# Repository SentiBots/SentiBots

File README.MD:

The SentiBots project is a project aiming to achieve the perfect distributed robotic system 
platform. By providing open source files we allow the end user to modify the files as necessary 
to his/her needs. This project invovles a custom designed frame and build which creates a 
modular, optimised frame for a distributed robotic system.

This is the source files for the SentiBots project. It includes the source code, cad files, build
notes and documentation you might need. 

# Cloning

```
git clone ssh://git@makerforce.io:222/SentiBots/SentiBots.git
cd SentiBots
git submodule init
git submodule update
```

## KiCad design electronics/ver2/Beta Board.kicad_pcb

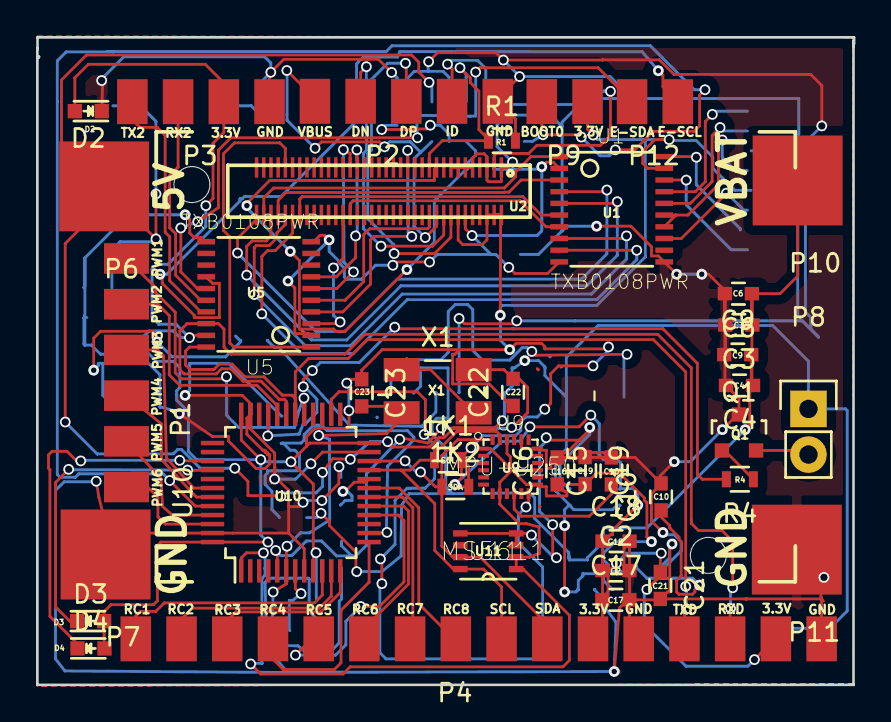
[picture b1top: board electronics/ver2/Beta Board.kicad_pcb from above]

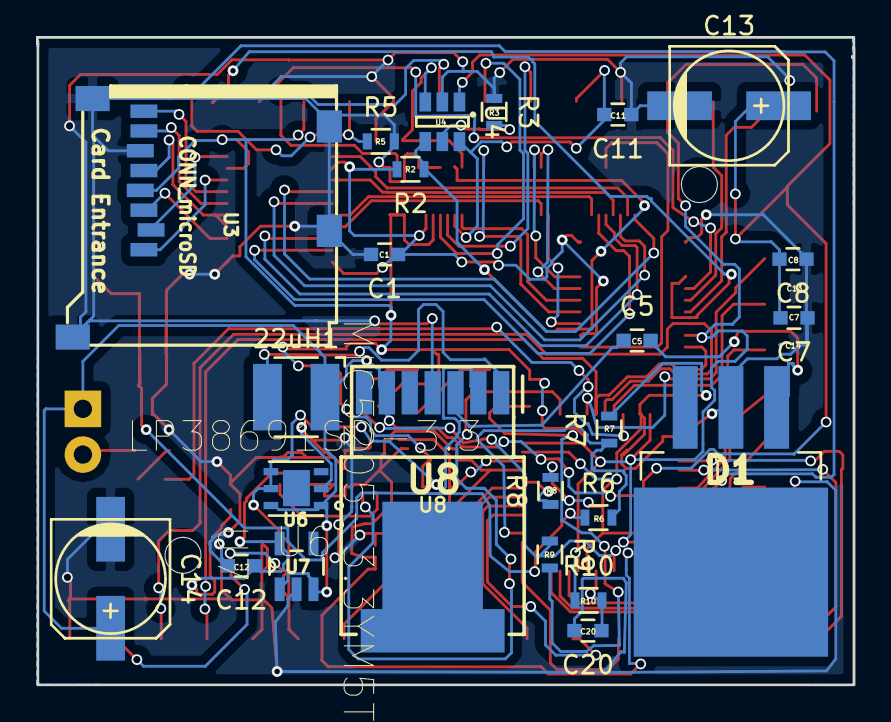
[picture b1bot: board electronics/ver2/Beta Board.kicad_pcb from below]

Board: 2 copper layers, 45.4 x 36.0 mm, 64 parts (24 on the bottom side), 71 nets.

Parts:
1K1, 1K2: R; R_0603
22uH1: INDUCTOR; NR4018
C1, C2, C8, C12, C15, C16, C17, C20, C21: 0.1uF; C_0603
C3, C4, C6: 15uF; C_0603
C5: 0.01uF; C_0603
C7: 1uF; C_0603
C9: 0.47uF; C_0603
C10: 10uF; C_0603
C11: 2.2uF; C_0603
C13, C14: 180uF; c_elec_6.3x5.8
C18, C19: 10nF; C_0603
C22, C23: 27pF; C_0603
D1: 6TQ045S; TO-263-3Lead
D2: RED; LED_0603
D3: GREEN; LED_0603
D4: YELLOW; LED_0603
P1: PWM; PAD1X6
P2: USB OTG; PAD1X5
P3: UART EDISON; PAD1X4
P4: MCU GPIO; PAD1X16
P6: 5V; PADBIG
P7, P11: GND; PADBIG
P8: BUZZER; Pin_Header_Straight_1x02
P9: BOOT; PAD1X2
P10: V_BATT; PADBIG
P12: I2C_EDISON; PAD1X2
Q1: MMBT3906; SOT-23
R1: 100K; R_0603
R2, R10: 10K; R_0603
R3: 536; R_0603
R4: 100R; R_0603
R5, R7, R8: 1K; R_0603
R6: 10k; R_0603
R9: 1M; R_0603
U1, U5: TXB0108PWR; TSSOP20
U2: EdisonConnector; EDISON_DAUGHTER
U3: CONN_microSD; Memory_Card_microSD_3M_290805
U4: MIC2039; SOT-23-6
U6: LP38691SD-3.3; DFN300X300X80-7N
U7: MIC5205-3.3YM5TR; SOT95P280X130-5N
U8: LM2678T-5.0; TO-263-7-TEXAS
U9: MPU-9250; QFN-24%2f3MM
U10: STM32F103CB; LQFP-48_7x7mm_Pitch0.5mm
U11: MS5611; QFN-8
X1: 8.000MHz/20p; Crystal_SMD_5032_4Pads

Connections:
1.8V: C1.1, R2.2, U1.2, U1.10, U2.12, U5.2, U5.10
3.3V: 1K1.2, 1K2.2, C2.1, C17.1, C18.1, C21.1, C22.1, C23.1, D2.2, D3.2, D4.2, P3.3, P4.11, P4.15, P9.2, R10.1, U1.19, U2.2, U2.4, U2.6, U2.14, U3.4, U5.19, U6.4, U6.5, U10.9, U10.24, U10.36, U10.48
3.3V_SEN: C10.1, C12.1, C16.1, C19.2, U7.5, U9.1, U9.8, U9.13, U9.22, U10.1, U11.1, U11.2
5V: 22uH1.1, C7.2, C8.2, C13.1, C14.1, P6.1, P8.1, U4.1, U6.1, U6.6, U7.1, U7.3, U8.6
BEEP: R4.2, U10.33
BOOT0: P9.1, R5.1, U10.44
BOOT1: R8.1, U10.20
EDI_RX: U2.61, U5.1
EDI_RX2: U2.22, U5.5
EDI_SCL1: U2.41, U5.7
EDI_SDA1: U2.43, U5.6
EDI_TX: U2.46, U5.3
EDI_TX2: U2.27, U5.4
FAULT: R2.1, U2.19, U4.4
GND: C1.2, C2.2, C3.2, C4.2, C6.2, C7.1, C8.1, C9.1, C10.2, C11.1, C12.2, C13.2, C14.2, C15.2, C16.2, C17.2, C18.2, C19.1, C20.2, C21.2, D1.2, D2.1, P2.5, P3.4, P4.12, P4.16, P7.1, P11.1, Q1.3, R1.2, R3.1, R5.2, R7.2, R8.2, U1.11, U2.1, U2.5, U2.9, U2.11, U2.13, U2.15, U3.6, U3.9, U4.2, U5.11, U6.2, U7.2, U8.4, U9.18, U9.20, U10.8, U10.23, U10.35, U10.47, U11.3, U11.4, U11.5
LED0: D3.1, U10.40
LED1: D4.1, U10.39
MPU_INT: U9.12, U10.26
NRST: C20.1, R10.2, U10.7
unnamed: 22uH1.2, U8.1
unnamed: C5.1, U8.3
unnamed: C5.2, D1.1
unnamed: C15.1, U9.10
unnamed: P8.2, Q1.2
unnamed: P12.1, U5.15
unnamed: P12.2, U5.14
unnamed: Q1.1, R4.1
unnamed: R3.2, U4.5
unnamed: U1.13, U3.3
unnamed: U1.14, U1.15, U3.5
unnamed: U1.16, U3.7
unnamed: U1.17, U3.8
unnamed: U1.18, U3.1
unnamed: U1.20, U3.2
OSC_IN: C22.2, R9.1, U10.5, X1.2
OSC_OUT: C23.2, R9.2, U10.6, X1.1
POWER_ADC: R6.2, R7.1, U10.14
PSW: R1.1, U2.21, U4.3
PWM1: P1.6, U10.29
PWM2: P1.5, U10.32
PWM3: P1.4, U10.42
PWM4: P1.3, U10.43
PWM5: P1.2, U10.45
PWN6: P1.1, U10.46
RC_CH1: P4.1, U10.10
RC_CH2: P4.2, U10.11
RC_CH3: P4.3, U10.12
RC_CH4: P4.4, U10.13
RC_CH5: P4.5, U10.16
RC_CH6: P4.6, U10.17
RC_CH7: P4.7, U10.18
RC_CH8: P4.8, U10.19
RX2: P3.2, U5.16
RXD: P4.14, U5.18, U10.31
SCL: 1K1.1, P4.9, U9.23, U10.21, U11.8
SDA: 1K2.1, P4.10, U9.24, U10.22, U11.7
SD_0_CD#: U1.9, U2.60
SD_0_CLK: U1.6, U2.58
SD_0_CMD: U1.8, U2.62
SD_0_DA3: U1.1, U2.68
SD_0_DAT0: U1.5, U2.66
SD_0_DAT1: U1.4, U2.70
SD_0_DAT2: U1.3, U2.64
SD_CLK_FB: U1.7, U2.44
TX2: P3.1, U5.17
TXD: P4.13, U5.20, U10.30
USB_DN: P2.2, U2.18
USB_DP: P2.3, U2.16
USB_ID: P2.4, U2.3
VBAT: C3.1, C4.1, C6.1, C9.2, P10.1, R6.1, U8.2
V_BUS: C11.2, P2.1, U2.20, U4.6

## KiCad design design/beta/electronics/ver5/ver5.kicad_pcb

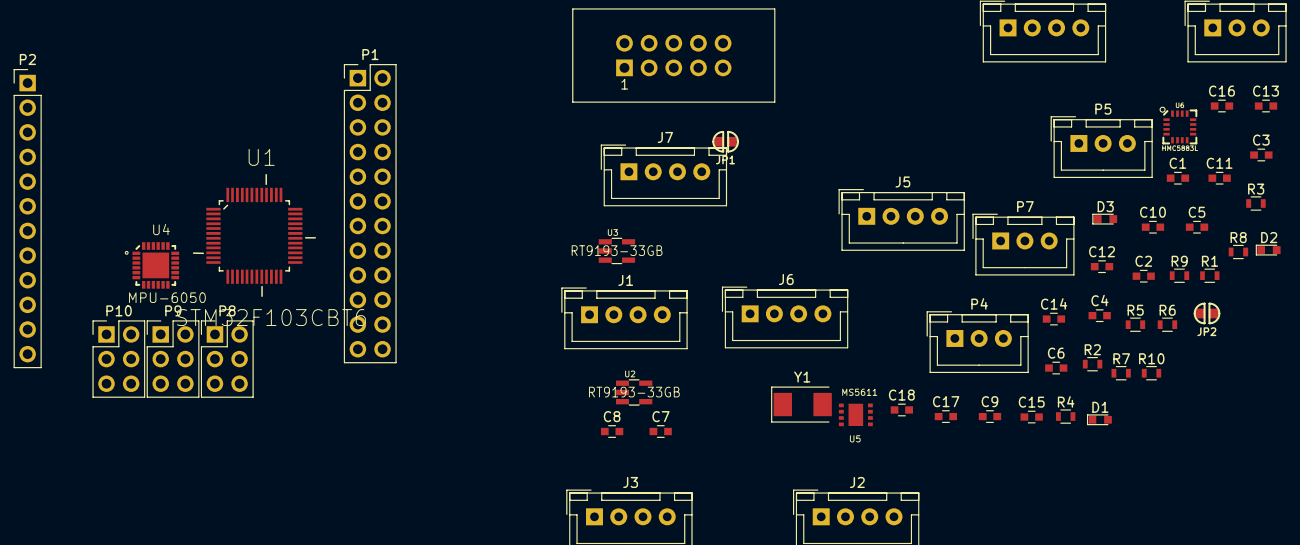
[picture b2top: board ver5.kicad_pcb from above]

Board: 2 copper layers, 57 parts (0 on the bottom side), 48 nets, no tracks yet.

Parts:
C1, C2, C3, C4: 10uF; C_0603
C5, C6, C9, C11, C12, C13, C16, C17, C18: 0.1uF; C_0603
C7: 4.7uF; C_0603
C8: 0.22uF; C_0603
C10: 2.2uF; C_0603
C14, C15: 18pF; C_0603
D1: BLUE; LED_0603
D2: RED; LED_0603
D3: GREEN; LED_0603
J1: NANOPI_UART2; JST_XH_B04B-XH-A_04x2.50mm_Straight
J2: NANOPI_USB1; JST_XH_B04B-XH-A_04x2.50mm_Straight
J3: NANOPI_USB2; JST_XH_B04B-XH-A_04x2.50mm_Straight
J4: STM32_I2C1; JST_XH_B04B-XH-A_04x2.50mm_Straight
J5: NANOPI_I2C1; JST_XH_B04B-XH-A_04x2.50mm_Straight
J6: STM32_UART1; JST_XH_B04B-XH-A_04x2.50mm_Straight
J7: STM32_UART2; JST_XH_B04B-XH-A_04x2.50mm_Straight
JP1, JP2: JUMPER; SOLDER-JUMPER_1-WAY
P1: NANOPI; Pin_Header_Straight_2x12_Pitch2.54mm
P2: NANOPI; Pin_Header_Straight_1x12_Pitch2.54mm
P3: JTAG; IDC_Header_Straight_10pins
P4: IR1; JST_XH_B03B-XH-A_03x2.50mm_Straight
P5: IR2; JST_XH_B03B-XH-A_03x2.50mm_Straight
P6: IR3; JST_XH_B03B-XH-A_03x2.50mm_Straight
P7: IR4; JST_XH_B03B-XH-A_03x2.50mm_Straight
P8: MOTORS1; Pin_Header_Straight_2x03_Pitch2.54mm
P9: MOTORS2; Pin_Header_Straight_2x03_Pitch2.54mm
P10: MOTORS3; Pin_Header_Straight_2x03_Pitch2.54mm
R1, R2, R3: 1K; R_0603
R4, R8, R10: R; R_0603
R5, R6, R9: 10K; R_0603
R7: 1k; R_0603
U1: STM32F103CBT6; QFP50P900X900X160-48N
U2, U3: RT9193-33GB; SOT-23-5
U4: MPU-6050; QFN50P400X400X95-25N
U5: MS5611; QFN-8
U6: HMC5883L; LPCC-16
Y1: 8MHz; Crystal_SMD_Abracon_ABM3-2pin_5.0x3.2mm

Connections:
+3V3: P1.1, P1.17
+5V: C1.1, C2.1, J2.3, J3.3, P1.2, P1.4, P8.3, P8.4, P9.3, P9.4, P10.3, P10.4
/BOOT0: JP2.1, R9.2, U1.44
/BOOT1: JP1.1, R5.2, U1.20
/CLK: P1.23, P6.1
/CS: P1.24, P7.1
/LED0: R8.2, U1.40
/LED1: R10.2, U1.39
/MISO: P1.21, P5.1
/MOSI: P1.19, P4.1
/MPU_INT: U1.26, U4.12
/NRST: P3.10, U1.7
/OSC_IN: C14.1, U1.5, Y1.1
/OSC_OUT: C15.1, U1.6, Y1.2
/PIUART1_TX: J6.2, P1.8, U1.31
/PIUART_RX: J6.1, P1.10, U1.30
/PIUART_RX2: J1.2, P1.22
/PIUART_TX2: J1.1, P1.11
/PI_SCL: J5.1, P1.5
/PI_SDA: J5.2, P1.3
/POWER_ADC: R6.2, R7.1, U1.14
/PWM1: P8.1, U1.29
/PWM2: P8.2, U1.32
/PWM3: P9.1, U1.42
/PWM4: P9.2, U1.43
/PWM5: P10.1, U1.45
/PWM6: P10.2, U1.46
/RX2: J7.2, U1.13
/SCL: J4.1, R2.2, R3.2, U1.21, U4.23, U5.8, U6.1
/SDA: J4.2, R1.2, U1.22, U4.24, U5.7, U6.16
/SWDCLK: P3.4, U1.37
/SWDIO: P3.2, U1.34
/TX2: J7.1, U1.12
/USB1_DN: J2.2, P2.10
/USB1_DP: J2.1, P2.11
/USB2_DN: J3.2, P2.8
/USB2_DP: J3.1, P2.9
/VCC_SENSE: C3.1, C5.1, C11.1, U4.13, U5.1, U5.2, U6.2
GND: C1.2, C2.2, C3.2, C4.2, C5.2, C6.2, C7.2, C9.2, C10.1, C11.2, C12.1, C13.2, C14.2, C15.2, C16.2, C17.2, C18.2, J1.4, J2.4, J3.4, J4.4, J5.4, J6.4, J7.4, P1.6, P1.9, P1.14, P1.20, P2.1, P3.3, P3.5, P4.3, P5.3, P6.3, P7.3, P8.5, P8.6, P9.5, P9.6, P10.5, P10.6, R4.2, R5.1, R7.2, R9.1, U1.8, U1.23, U1.35, U1.47, U4.1, U4.9, U4.11, U4.18, U5.3, U5.4, U5.5, U6.9, U6.11
unnamed: C7.1, U6.10
unnamed: C8.1, U6.12
unnamed: C8.2, U6.8
unnamed: C10.2, U4.20
unnamed: C12.2, U4.10
unnamed: D1.1, R4.1
unnamed: D2.1, R8.1
unnamed: D3.1, R10.1
VCC: C4.1, C6.1, C9.1, C13.1, C16.1, C17.1, C18.1, D1.2, D2.2, D3.2, J1.3, J4.3, J5.3, J6.3, J7.3, JP1.2, JP2.2, P3.1, P4.2, P5.2, P6.2, P7.2, R1.1, R2.1, R3.1, U1.1, U1.9, U1.24, U1.36, U1.48, U4.8, U6.4, U6.13

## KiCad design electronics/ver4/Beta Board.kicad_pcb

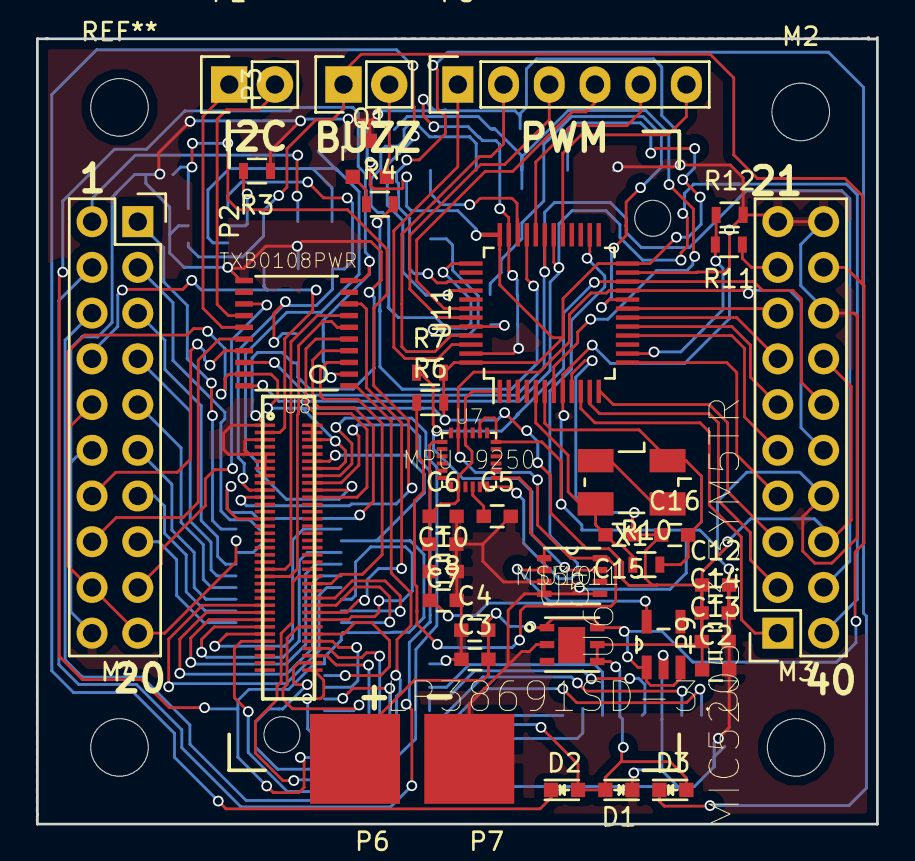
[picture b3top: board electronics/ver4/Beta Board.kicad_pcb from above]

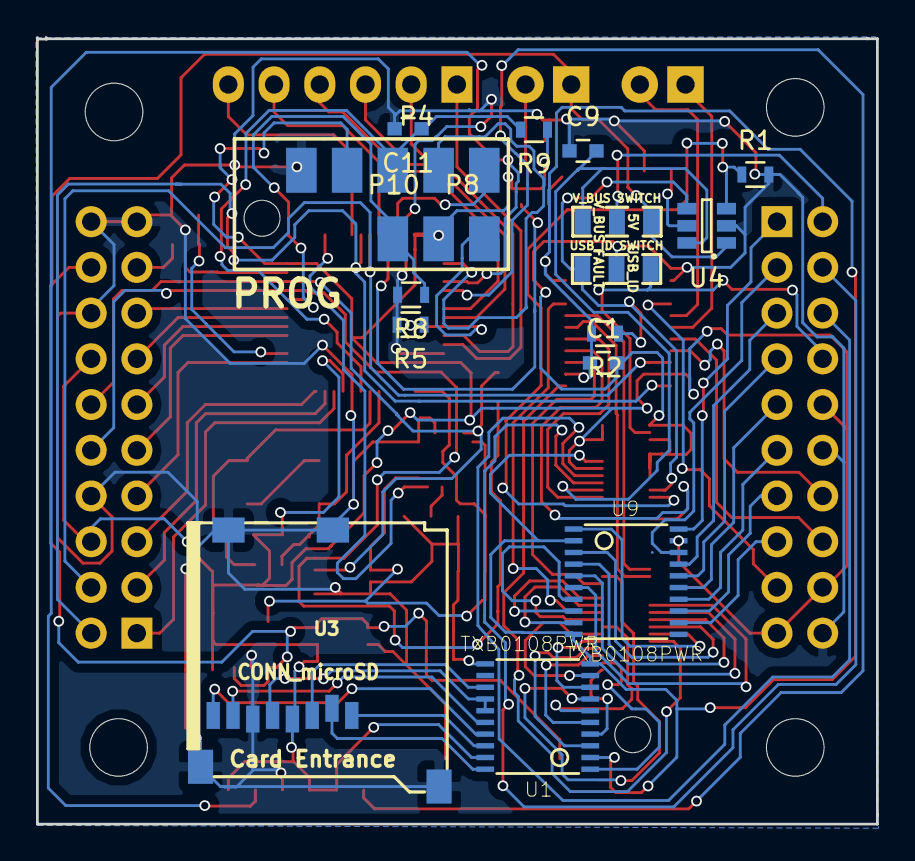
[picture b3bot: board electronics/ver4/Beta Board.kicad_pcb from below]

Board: 2 copper layers, 46.7 x 43.7 mm, 59 parts (17 on the bottom side), 89 nets.

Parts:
C1, C2, C4, C5, C6, C10, C11, C12, C14: 0.1uF; C_0603
C3: 1uF; C_0603
C7, C13: 10nF; C_0603
C8: 10uF; C_0603
C9: 2.2uF; C_0603
C15, C16: 27pF; C_0603
D1: RED; LED_0603
D2: GREEN; LED_0603
D3: YELLOW; LED_0603
M2, M3, M4: MountingHole_3.2mm_M3
P1: I2C_EDISON; Socket_Strip_Straight_1x02
P2: EDI_GPIO; Socket_Strip_Straight_2x10
P3: BUZZER; Pin_Header_Straight_1x02
P4: PROG; PAD1X5
P5: MCU_PWM; Socket_Strip_Straight_1x06
P6: 5V; PADBIG
P7: GND; PADBIG
P8: BOOT0; PAD1X2
P9: MCU_GPIO; Socket_Strip_Straight_2x10
P10: BOOT1; PAD1
Q1: MMBT3906; SOT-23
R1: 100K; R_0603
R2, R9: 10K; R_0603
R3: 536; R_0603
R4: 100R; R_0603
R5, R6, R7, R8, R12: 1K; R_0603
R10: 1M; R_0603
R11: 10k; R_0603
SW1: USB_ID SWITCH; 0805_Jumper
SW2: V_BUS SWITCH; 0805_Jumper
U1, U8, U9: TXB0108PWR; TSSOP20
U2: EdisonConnector; EDISON_DAUGHTER
U3: CONN_microSD; Memory_Card_microSD_3M_290805
U4: MIC2039; SOT-23-6
U5: LP38691SD-3.3; DFN300X300X80-7N
U6: MIC5205-3.3YM5TR; SOT95P280X130-5N
U7: MPU-9250; QFN-24%2f3MM
U10: MS5611; QFN-8
U11: STM32F103CB; LQFP-48_7x7mm_Pitch0.5mm
X1: 8.000MHz/20p; Crystal_SMD_5032_4Pads

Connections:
1.8V: C1.1, R2.2, U1.2, U1.10, U2.12, U8.2, U8.10, U9.2, U9.10
3.3V: C2.1, C12.1, C13.1, C14.1, C15.1, C16.1, D1.2, D2.2, D3.2, P2.10, P2.18, P2.19, P4.4, P8.2, P9.6, P9.14, R6.2, R7.2, R9.1, U1.19, U2.2, U2.4, U2.6, U2.14, U3.4, U5.4, U5.5, U8.19, U9.19, U11.9, U11.24, U11.36, U11.48
3.3V_SEN: C6.1, C7.2, C8.1, C10.1, U6.5, U7.1, U7.8, U7.13, U7.22, U10.1, U10.2, U11.1
5V: C3.2, C4.2, P3.1, P6.1, P9.18, SW2.1, U4.1, U5.1, U5.6, U6.1, U6.3
BEEP: R4.2, U11.33
BOOT0: P8.1, R5.1, U11.44
BOOT1: P10.1, R8.1, U11.20
EDI_RX: U2.61, U8.1
EDI_RX2: U2.22, U8.5
EDI_SCL1: U2.41, U8.7
EDI_SDA1: U2.43, U8.6
EDI_TX: U2.46, U8.3
EDI_TX2: U2.27, U8.4
FAULT: R2.1, SW1.3, U2.19, U4.4
GND: C1.2, C2.2, C3.1, C4.1, C5.2, C6.2, C7.1, C8.2, C9.1, C10.2, C11.2, C12.2, C13.2, C14.2, D1.1, P2.12, P2.20, P4.5, P7.1, P9.8, P9.16, P9.19, P9.20, Q1.3, R1.2, R3.1, R5.2, R8.2, R12.2, SW1.2, U1.11, U2.1, U2.5, U2.9, U2.11, U2.13, U2.15, U3.6, U3.9, U4.2, U5.2, U6.2, U7.18, U7.20, U8.11, U10.3, U10.4, U10.5, U11.8, U11.23, U11.35, U11.47
GPIO10: U2.59, U9.1
GPIO11: U2.57, U9.3
GPIO12: U2.55, U9.4
GPIO13: U2.53, U9.5
GPIO14: U2.51, U9.6
I2S_CLK: U2.52, U9.9
I2S_CLK2: P2.15, U9.12
I2S_FS: U2.54, U8.8
I2S_FS2: P2.17, U8.13
I2S_RXD: U2.50, U9.8
I2S_RXD2: P2.13, U9.13
I2S_TXD: U2.56, U9.7
I2S_TXD2: P2.11, U9.14
LED0: D2.1, U11.40
LED1: D3.1, U11.39
MPU_INT: U7.12, U11.26
NRST: C11.1, P4.3, R9.2, U11.7
unnamed: C5.1, U7.10
unnamed: P1.1, U8.15
unnamed: P1.2, U8.14
unnamed: P3.2, Q1.2
unnamed: Q1.1, R4.1
unnamed: R3.2, U4.5
unnamed: U1.13, U3.3
unnamed: U1.14, U1.15, U3.5
unnamed: U1.16, U3.7
unnamed: U1.17, U3.8
unnamed: U1.18, U3.1
unnamed: U1.20, U3.2
OSC_IN: C15.2, R10.1, U11.5, X1.2
OSC_OUT: C16.2, R10.2, U11.6, X1.1
POWER_ADC: R11.2, R12.1, U11.14
PSW: R1.1, U2.21, U4.3
PWM1: P5.6, U11.29
PWM2: P5.5, U11.32
PWM3: P5.4, U11.42
PWM4: P5.3, U11.43
PWM5: P5.2, U11.45
PWN6: P5.1, U11.46
RC_CH1: P9.1, U11.10
RC_CH2: P9.3, U11.11
RC_CH3: P9.5, U11.12
RC_CH4: P9.7, U11.13
RC_CH5: P9.9, U11.16
RC_CH6: P9.11, U11.17
RC_CH7: P9.13, U11.18
RC_CH8: P9.15, U11.19
RX2: P2.16, U8.16
RXD: P9.4, U8.18, U11.31
SCL: P9.10, R6.1, U7.23, U10.8, U11.21
SDA: P9.12, R7.1, U7.24, U10.7, U11.22
SD_0_CD#: U1.9, U2.60
SD_0_CLK: U1.6, U2.58
SD_0_CMD: U1.8, U2.62
SD_0_DA3: U1.1, U2.68
SD_0_DAT0: U1.5, U2.66
SD_0_DAT1: U1.4, U2.70
SD_0_DAT2: U1.3, U2.64
SD_CLK_FB: U1.7, U2.44
SPI_CLK: P2.5, U9.17
SPI_FS0: P2.7, U9.16
SPI_FS1: P2.9, U9.15
SPI_RXD: P2.1, U9.20
SPI_TXD: P2.3, U9.18
SWDCLK: P4.2, U11.37
SWDIO: P4.1, U11.34
TX2: P2.14, U8.17
TXD: P9.2, U8.20, U11.30
USB_DN: P2.4, U2.18
USB_DP: P2.6, U2.16
USB_ID: P2.8, SW1.1, U2.3
USB_POWER: P2.2, SW2.2
VBAT: P9.17, R11.1
V_BUS: C9.2, SW2.3, U2.20, U4.6

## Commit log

2015-12-09 add README
2015-12-12 Organised /Code
2015-12-12 Add changelog
2015-12-13 Changed serial reading in python viewer to SSH.
2015-12-13 Added Paramiko Library
2015-12-29 SentiBot gen 3
2015-12-31 Fixed errors in PCB
2015-12-31 TKKYIA report
2016-01-04 added SSEF report
2016-01-04 updated SSEF Report
2016-01-05 modified SSEF report
2016-01-06 updated TKKYIA report
2016-01-07 updated SSEF files
2016-01-08 added SSEF summary
2016-01-27 replaced IMU code
2016-01-27 added appropriate libraries
2016-02-22 Test.ino and Servo.ino added
2016-02-26 Gen 4- Black Knight
2016-03-03 updated poster design for SSEF
2016-03-03 changed gen 4 name to Amethyst
2016-03-05 MSP + UDP
    Added code to communicate over MSP, and a UDP forwarder.
2016-03-10 Gen 5: Iris
2016-03-10 Added gen 5 3D case files
2016-03-11 Iris 5030 prop version complete
2016-03-11 integrated APK submodule
2016-03-15 added Iris 3040 tri-blade 3D CAD files
2016-03-16 updated Iris 3040 3D files
2016-03-20 updated 3D files for Iris
2016-03-21 updated 3D filse for Iris
2016-03-21 changed gen 5 name from Iris to Iona
2016-03-22 added curvature on corners of Iona
2016-03-23 added powerpoint presentation
2016-03-25 added ppt
2016-03-30 Updated pin numbers
2016-03-30 updated SentiBot control
2016-03-30 meow
2016-03-31 edited control code
2016-03-31 transitions
2016-03-31 meow 2
2016-03-31 latest code for control
2016-03-31 IT SHOULD WORK NOW
2016-04-04 added formal report
2016-04-09 updated control code
2016-04-09 Adaptive PID Library
2016-04-09 Revert "Adaptive PID Library"
    This reverts commit 032cb5ac39136c6d833f060c17c06b7e8f5d0c88.
2016-04-09 Revert "Merged branch master into master"
    This reverts commit ecd8c60c3d8779e765b7073864f393f8b66c70f0.
2016-04-09 Revert "Merged branch master into master"
    This reverts commit 1762ae4e2da662af1bfa7314833a7914d230461b.
2016-04-09 Added Adaptive PID
2016-04-09 Revert "Revert "Merged branch master into master""
    This reverts commit a615c368b56e7832a3f2e519d9e7f5eeb5b7d644.
2016-04-09 Fixed Adaptive PID Direction Problem
2016-04-09 Changed Arduino Code to Test Servos
2016-04-09 modified msp-base
2016-04-19 Fixed Adaptive PID
2016-04-20 Renamed to Adaptive PID
2016-04-21 added EdiCopter schematics
2016-04-28 finished EdiCopter rev 1
2016-04-29 added OSHPark snapshots
2016-04-29 fixed minor soldermask clearance (EdiCopter)
2016-04-30 fixed more soldermask clearance issues
2016-04-30 fixed silkscreen and added branding
2016-05-01 Moved components out of repository
2016-05-01 Added website
2016-05-02 updated design files
2016-05-03 added fill
2016-05-09 Removed APKBuild Submodule
2016-05-09 updated code
2016-05-10 What is this?
2016-05-10 WHY DOES IT CASCADE
2016-05-30 finished EdiCopter Rev 2
2016-06-04 Updating design to latest
2016-06-04 updated design to latest
2016-07-23 updated design to latest & added SSC report
2016-09-13 added vscode files
2016-10-18 added frugal innovation report version 2
2016-10-31 added latest frugal innovation report
2016-11-10 updated report
2016-11-14 added updated report
2016-11-18 Mmmmmmaahaaahahahhhha.htnunhtnoeutnmwuewuwwwfffffff
2016-11-18 booo
2016-11-21 Meh.
2016-11-25 added content to the report
2016-11-25 finished application section of report
2016-11-27 Not done.
2016-11-28 I give up
2016-11-28 I'd continue another day.
2017-01-02 finished SSEF report
2017-01-03 formatted references
2017-01-03 formatted citations
2017-01-04 finished abstract
2017-02-25 reformatted
2017-05-10 Update gitmodules
2017-06-29 removed presentations as a submodule
2017-06-29 updated design, code and website to latest
2017-07-06 updated code to latest
2017-07-26 smth
2017-08-21 cleaning this up
2017-08-21 added design files back
2017-08-21 unpacking the design
2017-08-21 filtered the contents
